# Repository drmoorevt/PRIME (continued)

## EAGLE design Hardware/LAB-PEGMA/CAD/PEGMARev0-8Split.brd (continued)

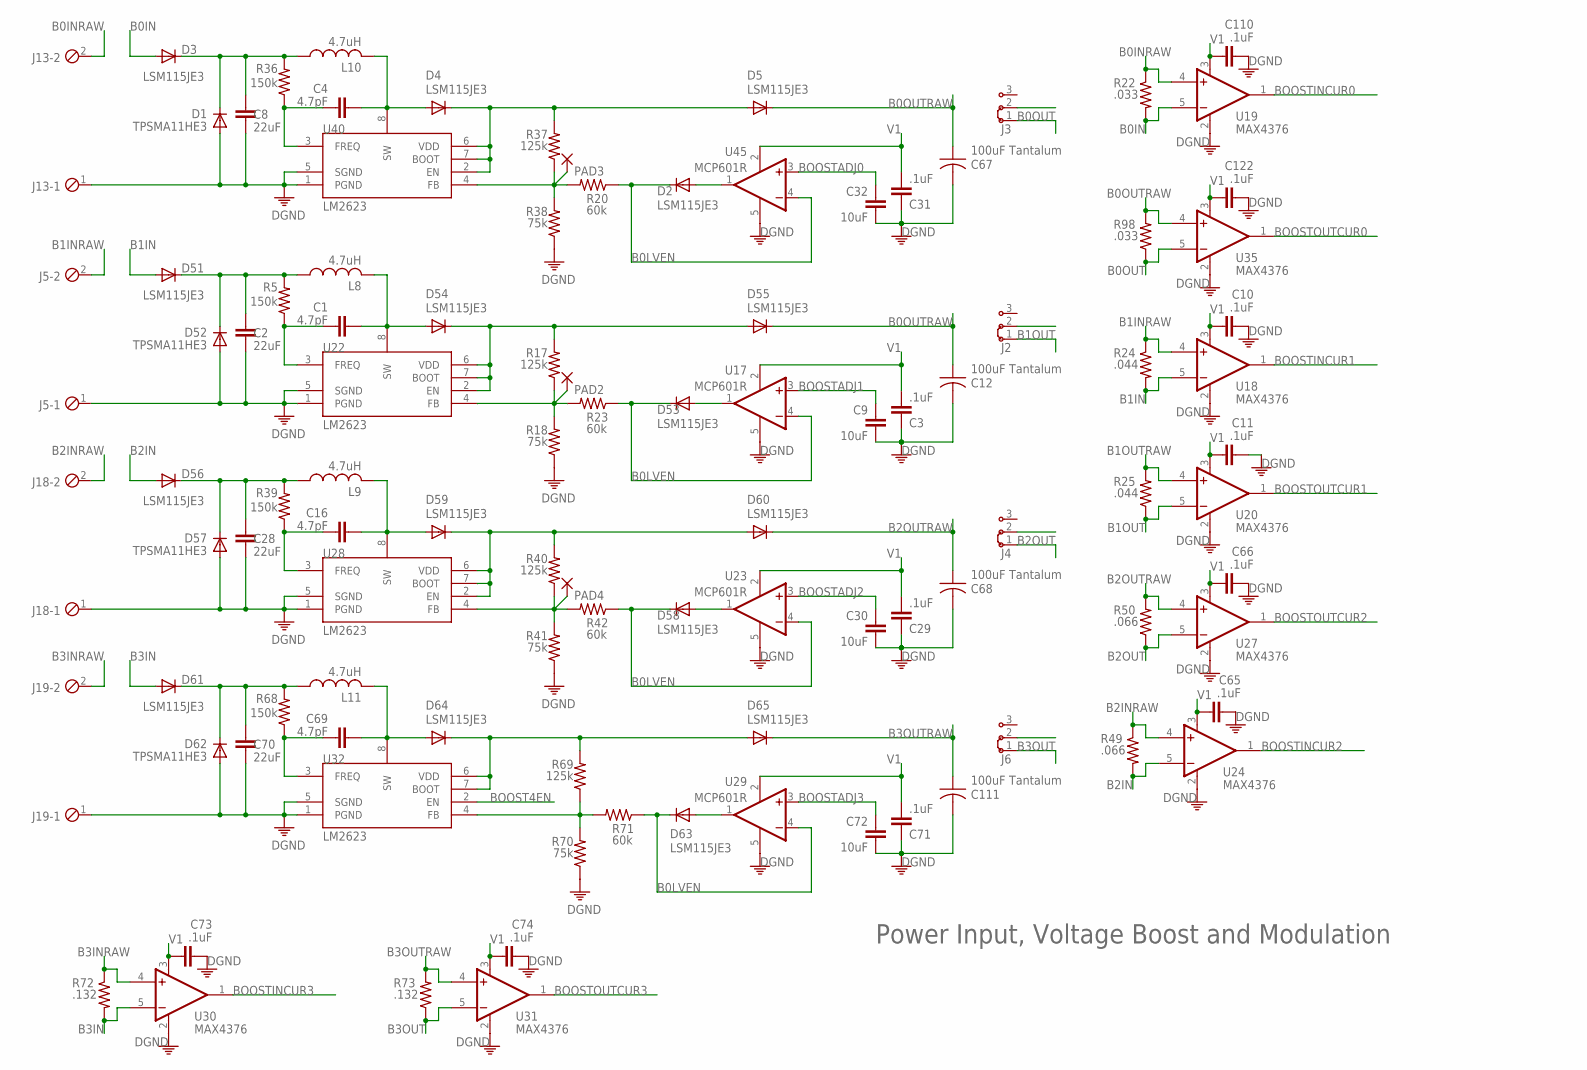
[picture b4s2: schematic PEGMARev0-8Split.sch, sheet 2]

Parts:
C1, C4, C16, C69: 4.7pF; C0603
C2, C8, C28, C70: 22uF; C0603
C3, C10, C11, C29, C31, C65, C66, C71, C73, C74, C110, C122: .1uF; C0603
C9, C30, C32, C72: 10uF; C0603
C12, C67, C68, C111: 100uF Tantalum; C1812
D1, D52, D57, D62: TPSMA11HE3; DO214AC
D2, D3, D4, D5, D51, D53, D54, D55, D56, D58, D59, D60, D61, D63, D64, D65: LSM115JE3; DO214BA
J2, J3, J4, J6: J2X2MM; 04C
J5, J13, J18, J19: MPT2; 2POL254
L8, L9, L10, L11: 4.7uH; L1008/2520METRIC
PAD2, PAD3, PAD4: 2,54/1,0
R5, R36, R39, R68: 150k; R0603
R17, R37, R40, R69: 125k; R0603
R18, R38, R41, R70: 75k; R0603
R20, R23, R42, R71: 60k; R0603
R22, R98: .033; R0603
R24, R25: .044; R0603
R49, R50: .066; R0603
R72, R73: .132; R0603
U17, U23, U29, U45: MCP601R; SOT23-5
U18, U19, U20, U24, U27, U30, U31, U35: MAX4376; SOT23-5
U22, U28, U32, U40: LM2623; MSOP8

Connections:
B0IN: D3.A, R22.2, U19.5 (-IN)
B0INRAW: J13.2, R22.1, U19.4 (+IN); also elsewhere on the board
B0LVEN: D2.C, D53.C, D58.C, D63.C, R20.1, R23.1, R42.1, R71.1, U17.4 (-IN), U23.4 (-IN), U29.4 (-IN), U45.4 (-IN); also elsewhere on the board
B0OUT: J3.1, R98.1, U35.5 (-IN)
B0OUTRAW: C12.1, C67.1, D5.C, D55.C, R98.2, U35.4 (+IN)
B1IN: D51.A, R24.2, U18.5 (-IN)
B1INRAW: J5.2, R24.1, U18.4 (+IN); also elsewhere on the board
B1OUT: J2.1, R25.1, U20.5 (-IN)
B1OUTRAW: R25.2, U20.4 (+IN)
B2IN: D56.A, R49.2, U24.5 (-IN)
B2INRAW: J18.2, R49.1, U24.4 (+IN); also elsewhere on the board
B2OUT: J4.1, R50.1, U27.5 (-IN)
B2OUTRAW: C68.1, D60.C, R50.2, U27.4 (+IN)
B3IN: D61.A, R72.2, U30.5 (-IN)
B3INRAW: J19.2, R72.1, U30.4 (+IN); also elsewhere on the board
B3OUT: J6.1, R73.1, U31.5 (-IN)
B3OUTRAW: C111.1, D65.C, R73.2, U31.4 (+IN)
BOOST4EN: U32.2 (EN); also elsewhere on the board
BOOSTADJ0: C32.1, U45.3 (+IN); also elsewhere on the board
BOOSTADJ1: C9.1, U17.3 (+IN); also elsewhere on the board
BOOSTADJ2: C30.1, U23.3 (+IN); also elsewhere on the board
BOOSTADJ3: C72.1, U29.3 (+IN); also elsewhere on the board
BOOSTINCUR0: U19.1 (OUT); also elsewhere on the board
BOOSTINCUR1: U18.1 (OUT); also elsewhere on the board
BOOSTINCUR2: U24.1 (OUT); also elsewhere on the board
BOOSTINCUR3: U30.1 (OUT); also elsewhere on the board
BOOSTOUTCUR0: U35.1 (OUT); also elsewhere on the board
BOOSTOUTCUR1: U20.1 (OUT); also elsewhere on the board
BOOSTOUTCUR2: U27.1 (OUT); also elsewhere on the board
BOOSTOUTCUR3: U31.1 (OUT); also elsewhere on the board
BUSVOUT: J2.2, J4.2, J6.2; also elsewhere on the board
unnamed: C8.2, D1.C, D3.C, L10.1, R36.2
unnamed: PAD3.1, R20.2, R37.1, R38.2, U40.4 (FB)
unnamed: C4.1, R36.1, U40.3 (FREQ)
unnamed: C2.2, D51.C, D52.C, L8.1, R5.2
unnamed: C4.2, D4.A, L10.2, U40.8 (SW)
unnamed: PAD2.1, R17.1, R18.2, R23.2, U22.4 (FB)
unnamed: C1.1, R5.1, U22.3 (FREQ)
unnamed: C1.2, D54.A, L8.2, U22.8 (SW)
unnamed: D4.C, D5.A, R37.2, U40.2 (EN), U40.6 (VDD), U40.7 (BOOT)
unnamed: D54.C, D55.A, R17.2, U22.2 (EN), U22.6 (VDD), U22.7 (BOOT)
unnamed: D53.A, U17.1 (OUT)
unnamed: D2.A, U45.1 (OUT)
unnamed: C28.2, D56.C, D57.C, L9.1, R39.2
unnamed: PAD4.1, R40.1, R41.2, R42.2, U28.4 (FB)
unnamed: C16.1, R39.1, U28.3 (FREQ)
unnamed: C16.2, D59.A, L9.2, U28.8 (SW)
unnamed: D59.C, D60.A, R40.2, U28.2 (EN), U28.6 (VDD), U28.7 (BOOT)
unnamed: D58.A, U23.1 (OUT)
unnamed: C70.2, D61.C, D62.C, L11.1, R68.2
unnamed: R69.1, R70.2, R71.2, U32.4 (FB)
unnamed: C69.1, R68.1, U32.3 (FREQ)
unnamed: C69.2, D64.A, L11.2, U32.8 (SW)
unnamed: D64.C, D65.A, R69.2, U32.6 (VDD), U32.7 (BOOT)
unnamed: D63.A, U29.1 (OUT)
PE: C2.1, C3.1, C8.1, C9.2, C10.1, C11.1, C12.2, C28.1, C29.1, C30.2, C31.1, C32.2, C65.1, C66.1, C67.2, C68.2, C70.1, C71.1, C72.2, C73.1, C74.1, C110.1, C111.2, C122.1, D1.A, D52.A, D57.A, D62.A, J5.1, J13.1, J18.1, J19.1, R18.1, R38.1, R41.1, R70.1, U17.5 (V-), U18.2 (V-), U19.2 (V-), U20.2 (V-), U22.1 (PGND), U22.5 (SGND), U23.5 (V-), U24.2 (V-), U27.2 (V-), U28.1 (PGND), U28.5 (SGND), U29.5 (V-), U30.2 (V-), U31.2 (V-), U32.1 (PGND), U32.5 (SGND), U35.2 (V-), U40.1 (PGND), U40.5 (SGND), U45.5 (V-); also elsewhere on the board
V1: C3.2, C10.2, C11.2, C29.2, C31.2, C65.2, C66.2, C71.2, C73.2, C74.2, C110.2, C122.2, U17.2 (V+), U18.3 (V+), U19.3 (V+), U20.3 (V+), U23.2 (V+), U24.3 (V+), U27.3 (V+), U29.2 (V+), U30.3 (V+), U31.3 (V+), U35.3 (V+), U45.2 (V+); also elsewhere on the board

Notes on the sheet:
Power Input, Voltage Boost and Modulation

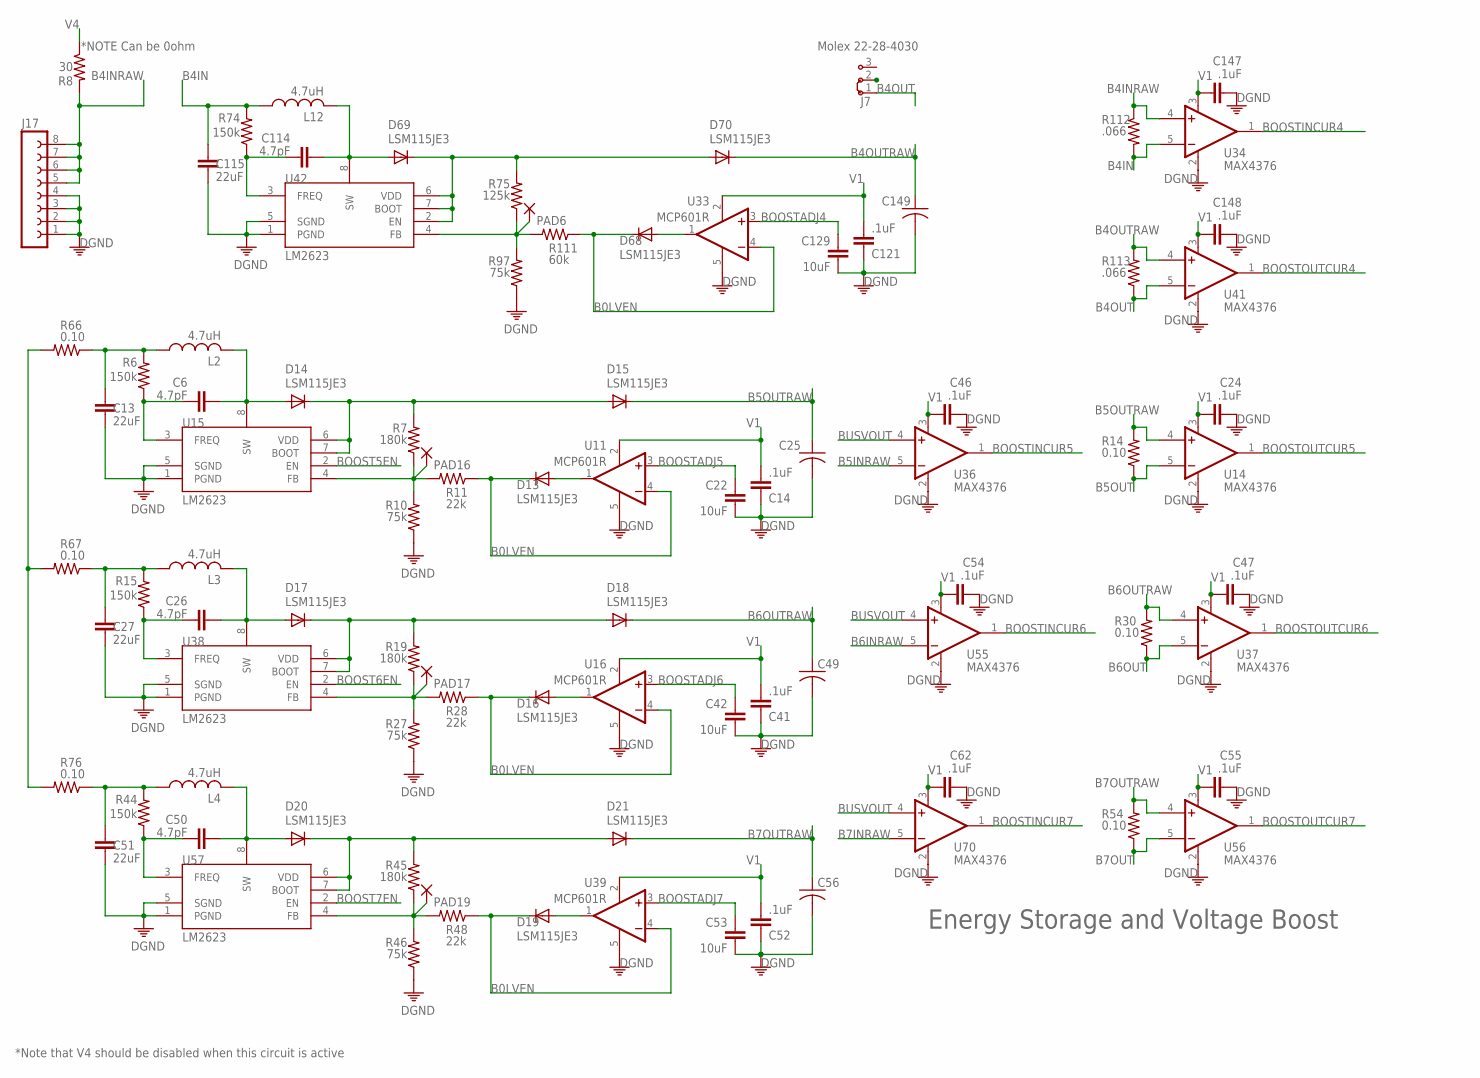
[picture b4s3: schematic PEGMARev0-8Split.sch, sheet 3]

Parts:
C6, C26, C50, C114: 4.7pF; C0603
C13, C27, C51, C115: 22uF; C0603
C14, C24, C41, C46, C47, C52, C54, C55, C62, C121, C147, C148: .1uF; C0603
C22, C42, C53, C129: 10uF; C0603
C25, C49, C56, C149: 100uF Tantalum; C1812
D13, D14, D15, D16, D17, D18, D19, D20, D21, D68, D69, D70: LSM115JE3; DO214BA
J7: Molex 22-28-4030; 04C
J17: FE08-1; FE08
L2, L3, L4, L12: 4.7uH; L1008/2520METRIC
PAD6, PAD16, PAD17, PAD19: 2,54/1,0
R6, R15, R44, R74: 150k; R0603
R7, R19, R45: 180k; R0603
R8: 30; R0603
R10, R27, R46, R97: 75k; R0603
R11, R28, R48: 22k; R0603
R14, R30, R54, R66, R67, R76: 0.10; R0603
R75: 125k; R0603
R111: 60k; R0603
R112, R113: .066; R0603
U11, U16, U33, U39: MCP601R; SOT23-5
U14, U34, U36, U37, U41, U55, U56, U70: MAX4376; SOT23-5
U15, U38, U42, U57: LM2623; MSOP8

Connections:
B0LVEN: D13.C, D16.C, D19.C, D68.C, R11.1, R28.1, R48.1, R111.1, U11.4 (-IN), U16.4 (-IN), U33.4 (-IN), U39.4 (-IN); also elsewhere on the board
B4IN: C115.2, L12.1, R74.2, R112.2, U34.5 (-IN)
B4INRAW: J17.5, J17.6, J17.7, J17.8, R8.2, R112.1, U34.4 (+IN); also elsewhere on the board
B4OUT: J7.1, R113.1, U41.5 (-IN)
B4OUTRAW: C149.1, D70.C, R113.2, U41.4 (+IN)
B5INRAW: C13.2, L2.1, R6.2, R66.1, U36.5 (-IN)
B5OUT: R14.1, U14.5 (-IN); also elsewhere on the board
B5OUTRAW: C25.1, D15.C, R14.2, U14.4 (+IN)
B6INRAW: C27.2, L3.1, R15.2, R67.1, U55.5 (-IN)
B6OUT: R30.1, U37.5 (-IN); also elsewhere on the board
B6OUTRAW: C49.1, D18.C, R30.2, U37.4 (+IN)
B7INRAW: C51.2, L4.1, R44.2, R76.1, U70.5 (-IN)
B7OUT: R54.1, U56.5 (-IN); also elsewhere on the board
B7OUTRAW: C56.1, D21.C, R54.2, U56.4 (+IN)
BOOST5EN: U15.2 (EN); also elsewhere on the board
BOOST6EN: U38.2 (EN); also elsewhere on the board
BOOST7EN: U57.2 (EN); also elsewhere on the board
BOOSTADJ4: C129.1, U33.3 (+IN); also elsewhere on the board
BOOSTADJ5: C22.1, U11.3 (+IN); also elsewhere on the board
BOOSTADJ6: C42.1, U16.3 (+IN); also elsewhere on the board
BOOSTADJ7: C53.1, U39.3 (+IN); also elsewhere on the board
BOOSTINCUR4: U34.1 (OUT); also elsewhere on the board
BOOSTINCUR5: U36.1 (OUT); also elsewhere on the board
BOOSTINCUR6: U55.1 (OUT); also elsewhere on the board
BOOSTINCUR7: U70.1 (OUT); also elsewhere on the board
BOOSTOUTCUR4: U41.1 (OUT); also elsewhere on the board
BOOSTOUTCUR5: U14.1 (OUT); also elsewhere on the board
BOOSTOUTCUR6: U37.1 (OUT); also elsewhere on the board
BOOSTOUTCUR7: U56.1 (OUT); also elsewhere on the board
BUSVOUT: J7.2, R66.2, R67.2, R76.2, U36.4 (+IN), U55.4 (+IN), U70.4 (+IN); also elsewhere on the board
unnamed: PAD16.1, R7.1, R10.2, R11.2, U15.4 (FB)
unnamed: C6.1, R6.1, U15.3 (FREQ)
unnamed: C6.2, D14.A, L2.2, U15.8 (SW)
unnamed: D14.C, D15.A, R7.2, U15.6 (VDD), U15.7 (BOOT)
unnamed: D13.A, U11.1 (OUT)
unnamed: PAD17.1, R19.1, R27.2, R28.2, U38.4 (FB)
unnamed: C26.1, R15.1, U38.3 (FREQ)
unnamed: C26.2, D17.A, L3.2, U38.8 (SW)
unnamed: D17.C, D18.A, R19.2, U38.6 (VDD), U38.7 (BOOT)
unnamed: D16.A, U16.1 (OUT)
unnamed: PAD19.1, R45.1, R46.2, R48.2, U57.4 (FB)
unnamed: C50.1, R44.1, U57.3 (FREQ)
unnamed: C50.2, D20.A, L4.2, U57.8 (SW)
unnamed: D20.C, D21.A, R45.2, U57.6 (VDD), U57.7 (BOOT)
unnamed: D19.A, U39.1 (OUT)
unnamed: PAD6.1, R75.1, R97.2, R111.2, U42.4 (FB)
unnamed: C114.1, R74.1, U42.3 (FREQ)
unnamed: C114.2, D69.A, L12.2, U42.8 (SW)
unnamed: D69.C, D70.A, R75.2, U42.2 (EN), U42.6 (VDD), U42.7 (BOOT)
unnamed: D68.A, U33.1 (OUT)
PE: C13.1, C14.1, C22.2, C24.1, C25.2, C27.1, C41.1, C42.2, C46.1, C47.1, C49.2, C51.1, C52.1, C53.2, C54.1, C55.1, C56.2, C62.1, C115.1, C121.1, C129.2, C147.1, C148.1, C149.2, J17.1, J17.2, J17.3, J17.4, R10.1, R27.1, R46.1, R97.1, U11.5 (V-), U14.2 (V-), U15.1 (PGND), U15.5 (SGND), U16.5 (V-), U33.5 (V-), U34.2 (V-), U36.2 (V-), U37.2 (V-), U38.1 (PGND), U38.5 (SGND), U39.5 (V-), U41.2 (V-), U42.1 (PGND), U42.5 (SGND), U55.2 (V-), U56.2 (V-), U57.1 (PGND), U57.5 (SGND), U70.2 (V-); also elsewhere on the board
V1: C14.2, C24.2, C41.2, C46.2, C47.2, C52.2, C54.2, C55.2, C62.2, C121.2, C147.2, C148.2, U11.2 (V+), U14.3 (V+), U16.2 (V+), U33.2 (V+), U34.3 (V+), U36.3 (V+), U37.3 (V+), U39.2 (V+), U41.3 (V+), U55.3 (V+), U56.3 (V+), U70.3 (V+); also elsewhere on the board
V4: R8.1; also elsewhere on the board

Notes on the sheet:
Energy Storage and Voltage Boost
*Note that V4 should be disabled when this circuit is active
*NOTE Can be 0ohm

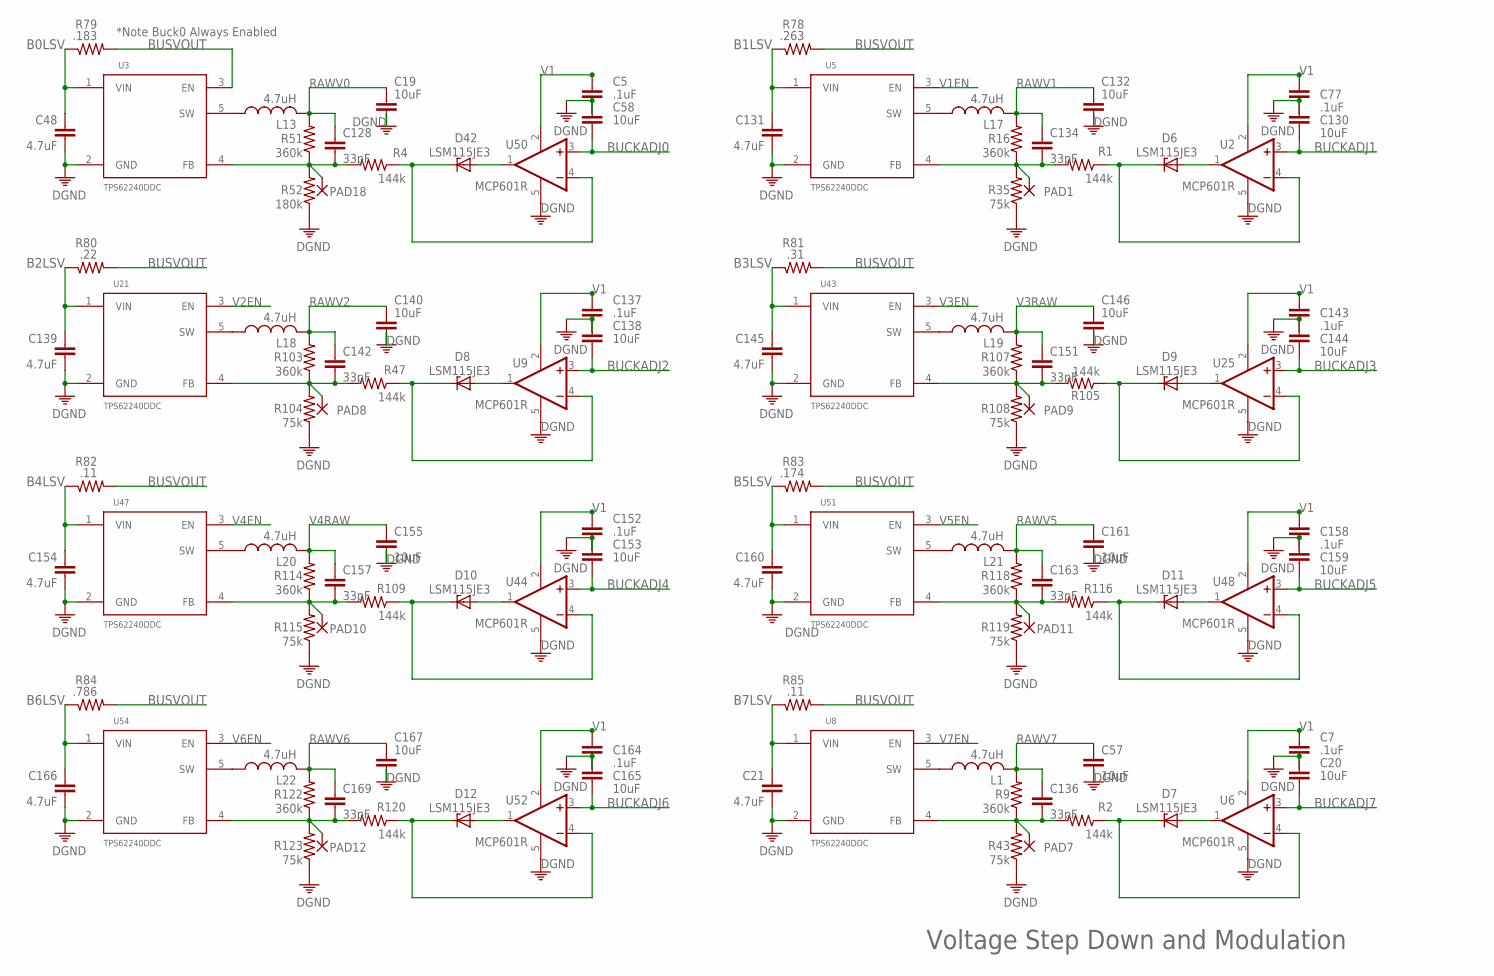
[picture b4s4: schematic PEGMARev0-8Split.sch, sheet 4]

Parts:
C5, C7, C77, C137, C143, C152, C158, C164: .1uF; C0603
C19, C20, C57, C58, C130, C132, C138, C140, C144, C146, C153, C155, C159, C161, C165, C167: 10uF; C0603
C21, C48, C131, C139, C145, C154, C160, C166: 4.7uF; C0603
C128, C134, C136, C142, C151, C157, C163, C169: 33pF; C0603
D6, D7, D8, D9, D10, D11, D12, D42: LSM115JE3; DO214BA
L1, L13, L17, L18, L19, L20, L21, L22: 4.7uH; L1008/2520METRIC
PAD1, PAD7, PAD8, PAD9, PAD10, PAD11, PAD12, PAD18: 2,54/1,0
R1, R2, R4, R47, R105, R109, R116, R120: 144k; R0603
R9, R16, R51, R103, R107, R114, R118, R122: 360k; R0603
R35, R43, R104, R108, R115, R119, R123: 75k; R0603
R52: 180k; R0603
R78: .263; R0603
R79: .183; R0603
R80: .22; R0603
R81: .31; R0603
R82, R85: .11; R0603
R83: .174; R0603
R84: .786; R0603
U2, U6, U9, U25, U44, U48, U50, U52: MCP601R; SOT23-5
U3, U5, U8, U21, U43, U47, U51, U54: TPS62240DDC; SOT23-5

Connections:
B0LSV: C48.1, R79.1, U3.1 (VIN)
B1LSV: C131.1, R78.1, U5.1 (VIN); also elsewhere on the board
B2LSV: C139.1, R80.1, U21.1 (VIN); also elsewhere on the board
B3LSV: C145.1, R81.1, U43.1 (VIN); also elsewhere on the board
B4LSV: C154.1, R82.1, U47.1 (VIN); also elsewhere on the board
B5LSV: C160.1, R83.1, U51.1 (VIN); also elsewhere on the board
B6LSV: C166.1, R84.1, U54.1 (VIN); also elsewhere on the board
B7LSV: C21.1, R85.1, U8.1 (VIN); also elsewhere on the board
BUCKADJ0: C58.1, U50.3 (+IN); also elsewhere on the board
BUCKADJ1: C130.1, U2.3 (+IN); also elsewhere on the board
BUCKADJ2: C138.1, U9.3 (+IN); also elsewhere on the board
BUCKADJ3: C144.1, U25.3 (+IN); also elsewhere on the board
BUCKADJ4: C153.1, U44.3 (+IN); also elsewhere on the board
BUCKADJ5: C159.1, U48.3 (+IN); also elsewhere on the board
BUCKADJ6: C165.1, U52.3 (+IN); also elsewhere on the board
BUCKADJ7: C20.1, U6.3 (+IN); also elsewhere on the board
BUSVOUT: R78.2, R79.2, R80.2, R81.2, R82.2, R83.2, R84.2, R85.2, U3.3 (EN); also elsewhere on the board
unnamed: D42.C, R4.1, U50.4 (-IN)
unnamed: L13.1, U3.5 (SW)
unnamed: D7.C, R2.1, U6.4 (-IN)
unnamed: C136.2, PAD7.1, R2.2, R9.1, R43.2, U8.4 (FB)
unnamed: L1.1, U8.5 (SW)
unnamed: D6.C, R1.1, U2.4 (-IN)
unnamed: D7.A, U6.1 (OUT)
unnamed: C134.2, PAD1.1, R1.2, R16.1, R35.2, U5.4 (FB)
unnamed: C128.2, PAD18.1, R4.2, R51.1, R52.2, U3.4 (FB)
unnamed: L17.1, U5.5 (SW)
unnamed: D6.A, U2.1 (OUT)
unnamed: D8.C, R47.1, U9.4 (-IN)
unnamed: C142.2, PAD8.1, R47.2, R103.1, R104.2, U21.4 (FB)
unnamed: L18.1, U21.5 (SW)
unnamed: D8.A, U9.1 (OUT)
unnamed: D42.A, U50.1 (OUT)
unnamed: D9.C, R105.1, U25.4 (-IN)
unnamed: C151.2, PAD9.1, R105.2, R107.1, R108.2, U43.4 (FB)
unnamed: L19.1, U43.5 (SW)
unnamed: D9.A, U25.1 (OUT)
unnamed: D10.C, R109.1, U44.4 (-IN)
unnamed: C157.2, PAD10.1, R109.2, R114.1, R115.2, U47.4 (FB)
unnamed: L20.1, U47.5 (SW)
unnamed: D10.A, U44.1 (OUT)
unnamed: D11.C, R116.1, U48.4 (-IN)
unnamed: C163.2, PAD11.1, R116.2, R118.1, R119.2, U51.4 (FB)
unnamed: L21.1, U51.5 (SW)
unnamed: D11.A, U48.1 (OUT)
unnamed: D12.C, R120.1, U52.4 (-IN)
unnamed: C169.2, PAD12.1, R120.2, R122.1, R123.2, U54.4 (FB)
unnamed: L22.1, U54.5 (SW)
unnamed: D12.A, U52.1 (OUT)
PE: C5.1, C7.1, C19.2, C20.2, C21.2, C48.2, C57.2, C58.2, C77.1, C130.2, C131.2, C132.2, C137.1, C138.2, C139.2, C140.2, C143.1, C144.2, C145.2, C146.2, C152.1, C153.2, C154.2, C155.2, C158.1, C159.2, C160.2, C161.2, C164.1, C165.2, C166.2, C167.2, R35.1, R43.1, R52.1, R104.1, R108.1, R115.1, R119.1, R123.1, U2.5 (V-), U3.2 (GND), U5.2 (GND), U6.5 (V-), U8.2 (GND), U9.5 (V-), U21.2 (GND), U25.5 (V-), U43.2 (GND), U44.5 (V-), U47.2 (GND), U48.5 (V-), U50.5 (V-), U51.2 (GND), U52.5 (V-), U54.2 (GND); also elsewhere on the board
RAWV0: C19.1, C128.1, L13.2, R51.2; also elsewhere on the board
RAWV1: C132.1, C134.1, L17.2, R16.2; also elsewhere on the board
RAWV2: C140.1, C142.1, L18.2, R103.2; also elsewhere on the board
RAWV5: C161.1, C163.1, L21.2, R118.2; also elsewhere on the board
RAWV6: C167.1, C169.1, L22.2, R122.2; also elsewhere on the board
RAWV7: C57.1, C136.1, L1.2, R9.2; also elsewhere on the board
V1: C5.2, C7.2, C77.2, C137.2, C143.2, C152.2, C158.2, C164.2, U2.2 (V+), U6.2 (V+), U9.2 (V+), U25.2 (V+), U44.2 (V+), U48.2 (V+), U50.2 (V+), U52.2 (V+); also elsewhere on the board
V1EN: U5.3 (EN); also elsewhere on the board
V2EN: U21.3 (EN); also elsewhere on the board
V3EN: U43.3 (EN); also elsewhere on the board
V3RAW: C146.1, C151.1, L19.2, R107.2
V4EN: U47.3 (EN); also elsewhere on the board
V4RAW: C155.1, C157.1, L20.2, R114.2
V5EN: U51.3 (EN); also elsewhere on the board
V6EN: U54.3 (EN); also elsewhere on the board
V7EN: U8.3 (EN); also elsewhere on the board

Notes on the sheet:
*Note Buck0 Always Enabled
Voltage Step Down and Modulation

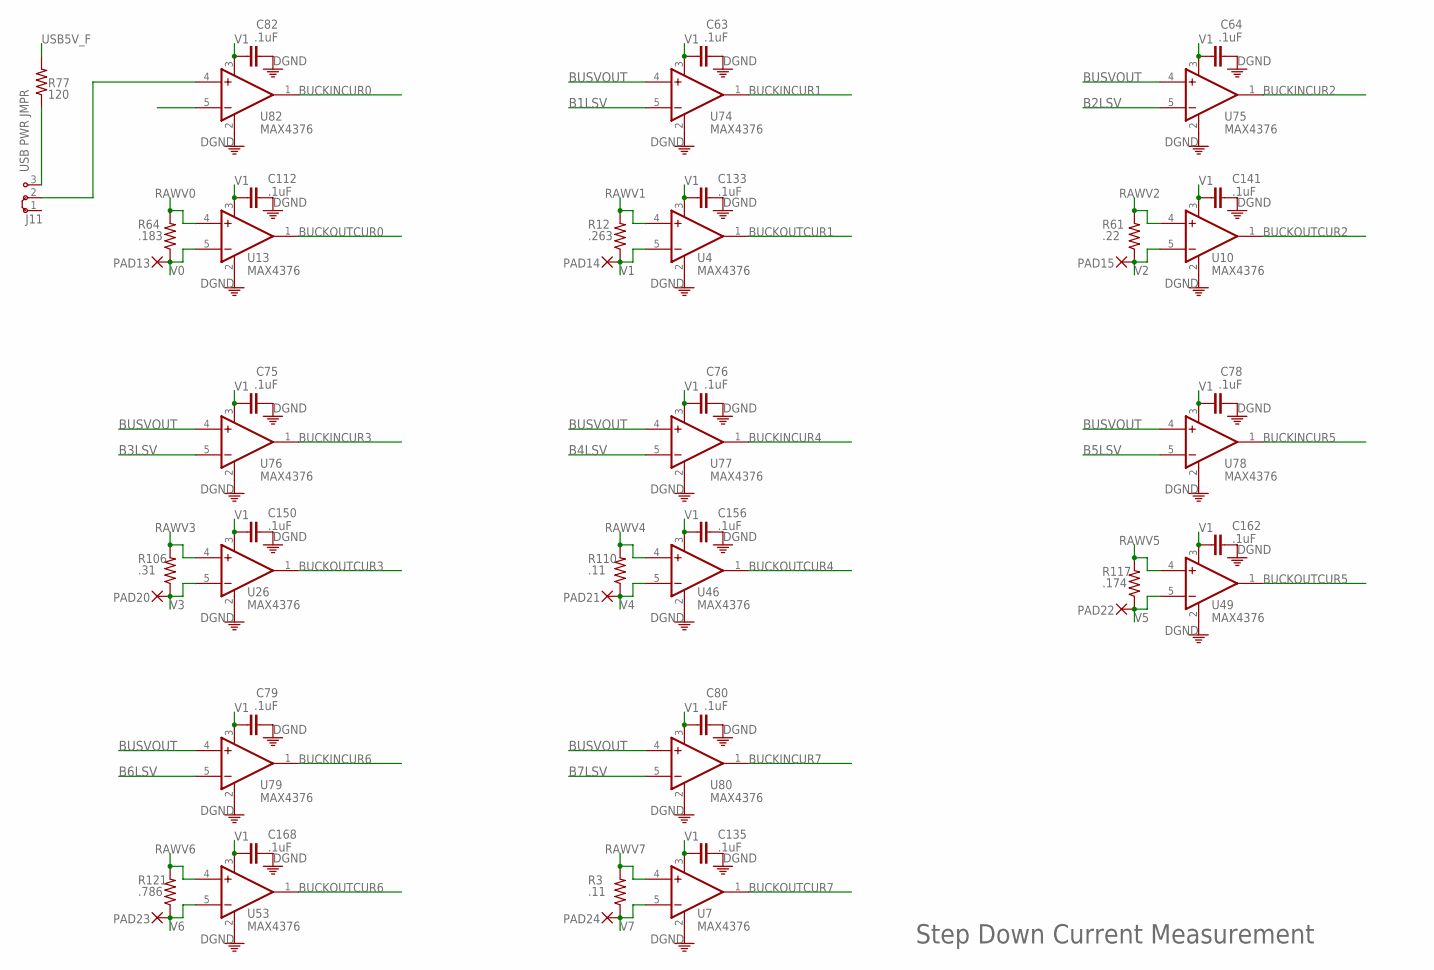
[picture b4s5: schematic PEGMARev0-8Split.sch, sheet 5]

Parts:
C63, C64, C75, C76, C78, C79, C80, C82, C112, C133, C135, C141, C150, C156, C162, C168: .1uF; C0603
J11: J2X2MM; 04C
PAD13, PAD14, PAD15, PAD20, PAD21, PAD22, PAD23, PAD24: 2,54/1,0
R3, R110: .11; R0603
R12: .263; R0603
R61: .22; R0603
R64: .183; R0603
R77: 120; M1206
R106: .31; R0603
R117: .174; R0603
R121: .786; R0603
U4, U7, U10, U13, U26, U46, U49, U53, U74, U75, U76, U77, U78, U79, U80, U82: MAX4376; SOT23-5

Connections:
B1LSV: U74.5 (-IN); also elsewhere on the board
B2LSV: U75.5 (-IN); also elsewhere on the board
B3LSV: U76.5 (-IN); also elsewhere on the board
B4LSV: U77.5 (-IN); also elsewhere on the board
B5LSV: U78.5 (-IN); also elsewhere on the board
B6LSV: U79.5 (-IN); also elsewhere on the board
B7LSV: U80.5 (-IN); also elsewhere on the board
BUCKINCUR0: U82.1 (OUT); also elsewhere on the board
BUCKINCUR1: U74.1 (OUT); also elsewhere on the board
BUCKINCUR2: U75.1 (OUT); also elsewhere on the board
BUCKINCUR3: U76.1 (OUT); also elsewhere on the board
BUCKINCUR4: U77.1 (OUT); also elsewhere on the board
BUCKINCUR5: U78.1 (OUT); also elsewhere on the board
BUCKINCUR6: U79.1 (OUT); also elsewhere on the board
BUCKINCUR7: U80.1 (OUT); also elsewhere on the board
BUCKOUTCUR0: U13.1 (OUT); also elsewhere on the board
BUCKOUTCUR1: U4.1 (OUT); also elsewhere on the board
BUCKOUTCUR2: U10.1 (OUT); also elsewhere on the board
BUCKOUTCUR3: U26.1 (OUT); also elsewhere on the board
BUCKOUTCUR4: U46.1 (OUT); also elsewhere on the board
BUCKOUTCUR5: U49.1 (OUT); also elsewhere on the board
BUCKOUTCUR6: U53.1 (OUT); also elsewhere on the board
BUCKOUTCUR7: U7.1 (OUT); also elsewhere on the board
BUSVOUT: J11.2, U74.4 (+IN), U76.4 (+IN), U77.4 (+IN), U78.4 (+IN), U80.4 (+IN), U82.4 (+IN); also elsewhere on the board
PE: C63.1, C64.1, C75.1, C76.1, C78.1, C79.1, C80.1, C82.1, C112.1, C133.1, C135.1, C141.1, C150.1, C156.1, C162.1, C168.1, U4.2 (V-), U7.2 (V-), U10.2 (V-), U13.2 (V-), U26.2 (V-), U46.2 (V-), U49.2 (V-), U53.2 (V-), U74.2 (V-), U75.2 (V-), U76.2 (V-), U77.2 (V-), U78.2 (V-), U79.2 (V-), U80.2 (V-), U82.2 (V-); also elsewhere on the board
RAWV0: R64.2, U13.4 (+IN); also elsewhere on the board
RAWV1: R12.2, U4.4 (+IN); also elsewhere on the board
RAWV2: R61.2, U10.4 (+IN); also elsewhere on the board
RAWV3: R106.2, U26.4 (+IN)
RAWV4: R110.2, U46.4 (+IN)
RAWV5: R117.2, U49.4 (+IN); also elsewhere on the board
RAWV6: R121.2, U53.4 (+IN); also elsewhere on the board
RAWV7: R3.2, U7.4 (+IN); also elsewhere on the board
USB5V_F: J11.3, R77.1, R77.2; also elsewhere on the board
V0: PAD13.1, R64.1, U13.5 (-IN); also elsewhere on the board
V1: C63.2, C64.2, C75.2, C76.2, C78.2, C79.2, C80.2, C82.2, C112.2, C133.2, C135.2, C141.2, C150.2, C156.2, C162.2, C168.2, PAD14.1, R12.1, U4.3 (V+), U4.5 (-IN), U7.3 (V+), U10.3 (V+), U13.3 (V+), U26.3 (V+), U46.3 (V+), U49.3 (V+), U53.3 (V+), U74.3 (V+), U75.3 (V+), U76.3 (V+), U77.3 (V+), U78.3 (V+), U79.3 (V+), U80.3 (V+), U82.3 (V+); also elsewhere on the board
V2: PAD15.1, R61.1, U10.5 (-IN); also elsewhere on the board
V3: PAD20.1, R106.1, U26.5 (-IN); also elsewhere on the board
V4: PAD21.1, R110.1, U46.5 (-IN); also elsewhere on the board
V5: PAD22.1, R117.1, U49.5 (-IN); also elsewhere on the board
V6: PAD23.1, R121.1, U53.5 (-IN); also elsewhere on the board
V7: PAD24.1, R3.1, U7.5 (-IN); also elsewhere on the board

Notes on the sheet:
USB PWR JMPR
Step Down Current Measurement

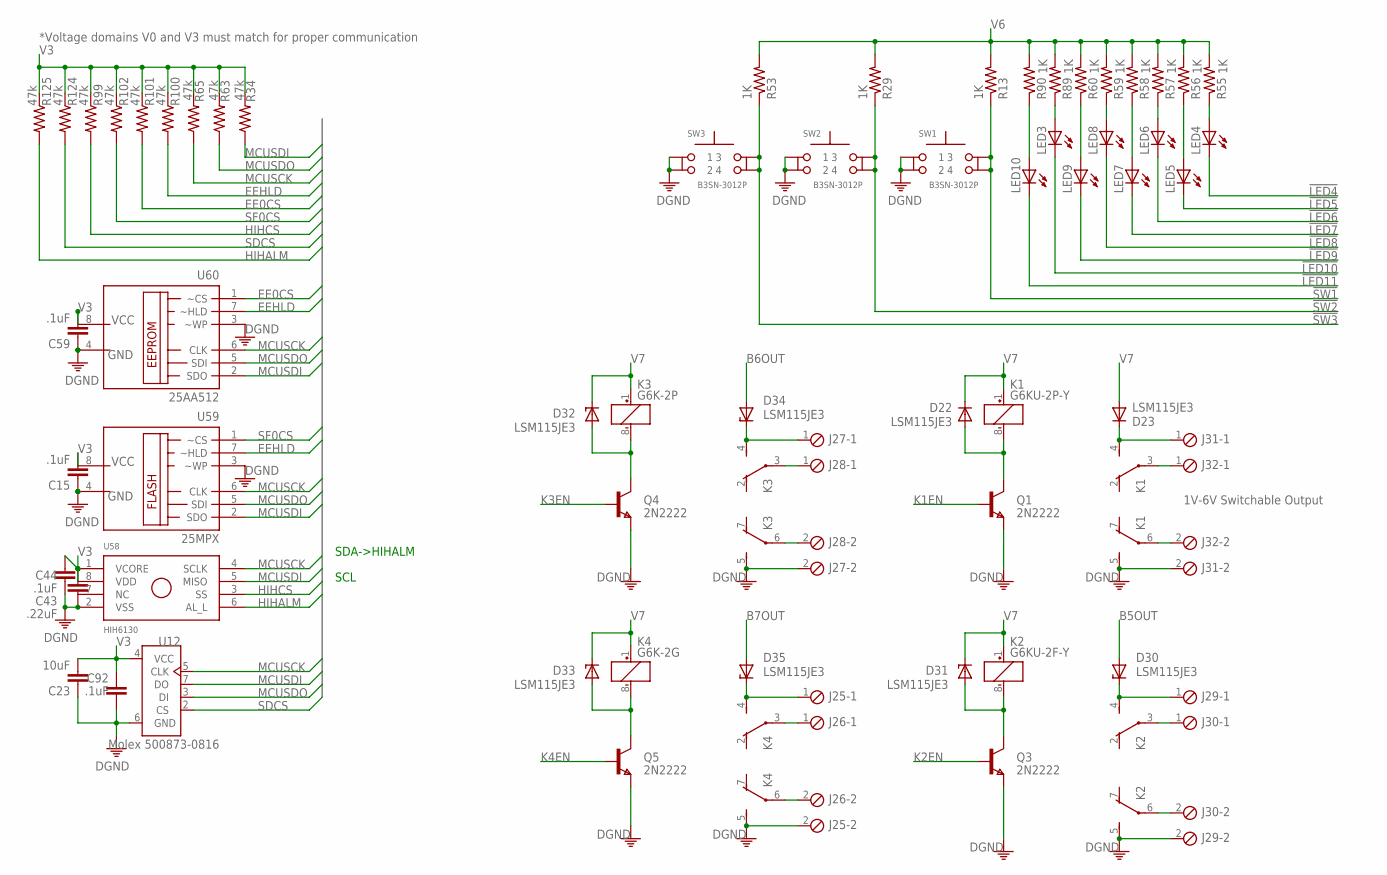
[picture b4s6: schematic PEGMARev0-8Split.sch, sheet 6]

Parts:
C15, C44, C59, C92: .1uF; C0603
C23: 10uF; C0603
C43: .22uF; C0603
D22, D23, D30, D31, D32, D33, D34, D35: LSM115JE3; DO214BA
J25, J26, J27, J28, J29, J30, J31, J32: MPT2; 2POL254
K1: G6KU-2P-Y
K2: G6KU-2F-Y
K3: G6K-2P
K4: G6K-2G
LED3, LED4, LED5, LED6, LED7, LED8, LED9, LED10: LEDCHIPLED_1206; CHIPLED_1206
Q1, Q3, Q4, Q5: 2N2222; SOT323
R13, R29, R53, R55, R56, R57, R58, R59, R60, R89, R90: 1K; R0603
R34, R63, R65, R99, R100, R101, R102, R124, R125: 47k; R0603
SW1, SW2, SW3: B3SN-3012P; SWITCH(B3SN)
U12: Molex 500873-0816; MICROSD
U58: HIH6130; SO-08M
U59: 25MPX; SO-08M
U60: 25AA512; SO-08M

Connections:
!LED4: LED4.C; also elsewhere on the board
!LED5: LED5.C; also elsewhere on the board
!LED6: LED6.C; also elsewhere on the board
!LED7: LED7.C; also elsewhere on the board
!LED8: LED8.C; also elsewhere on the board
!LED9: LED9.C; also elsewhere on the board
!LED10: LED3.C; also elsewhere on the board
!LED11: LED10.C; also elsewhere on the board
!SW1: R13.1, SW1.3, SW1.4; also elsewhere on the board
!SW2: R29.1, SW2.3, SW2.4; also elsewhere on the board
!SW3: R53.1, SW3.3, SW3.4; also elsewhere on the board
B5OUT: D30.A; also elsewhere on the board
B6OUT: D34.A; also elsewhere on the board
B7OUT: D35.A; also elsewhere on the board
EE0CS: R101.2, U60.1 (~CS); also elsewhere on the board
EEHLD: R100.2, U59.7 (~HLD), U60.7 (~HLD); also elsewhere on the board
HIHALM: R125.2, U58.6 (AL_L); also elsewhere on the board
HIHCS: R99.2, U58.3 (SS); also elsewhere on the board
K1EN: Q1.2 (B); also elsewhere on the board
K2EN: Q3.2 (B); also elsewhere on the board
K3EN: Q4.2 (B); also elsewhere on the board
K4EN: Q5.2 (B); also elsewhere on the board
MCUSCK: R65.1, U12.5 (CLK), U58.4 (SCLK), U59.6 (CLK), U60.6 (CLK); also elsewhere on the board
MCUSDI: R34.1, U12.7 (DO), U58.5 (MISO), U59.2 (SDO), U60.2 (SDO); also elsewhere on the board
MCUSDO: R63.1, U12.3 (DI), U59.5 (SDI), U60.5 (SDI); also elsewhere on the board
unnamed: D31.A, K2.8 (-), Q3.1 (C)
unnamed: D22.A, K1.8 (-), Q1.1 (C)
unnamed: LED3.A, R89.1
unnamed: LED4.A, R55.1
unnamed: LED5.A, R56.1
unnamed: LED6.A, R57.1
unnamed: LED10.A, R90.1
unnamed: LED7.A, R58.1
unnamed: LED8.A, R59.1
unnamed: LED9.A, R60.1
unnamed: J32.1, K1.3
unnamed: J32.2, K1.6
unnamed: D32.A, K3.8 (-), Q4.1 (C)
unnamed: J28.1, K3.3
unnamed: D23.C, J31.1, K1.4 (S)
unnamed: J28.2, K3.6
unnamed: D33.A, K4.8 (-), Q5.1 (C)
unnamed: J30.1, K2.3
unnamed: D30.C, J29.1, K2.4 (S)
unnamed: J30.2, K2.6
unnamed: D34.C, J27.1, K3.4 (S)
unnamed: D35.C, J25.1, K4.4 (S)
unnamed: J26.1, K4.3
unnamed: J26.2, K4.6
PE: C15.1, C23.1, C43.1, C44.1, C59.1, C92.2, J25.2, J27.2, J29.2, J31.2, K1.5 (S), K2.5 (S), K3.5 (S), K4.5 (S), Q1.3 (E), Q3.3 (E), Q4.3 (E), Q5.3 (E), SW1.1, SW1.2, SW2.1, SW2.2, SW3.1, SW3.2, U12.6 (GND), U58.2 (VSS), U59.3 (~WP), U59.4 (GND), U60.3 (~WP), U60.4 (GND); also elsewhere on the board
SDCS: R124.2, U12.2 (CS); also elsewhere on the board
SF0CS: R102.2, U59.1 (~CS); also elsewhere on the board
V3: C15.2, C23.2, C43.2, C44.2, C59.2, C92.1, R34.2, R63.2, R65.2, R99.1, R100.1, R101.1, R102.1, R124.1, R125.1, U12.4 (VCC), U58.1 (VCORE), U58.8 (VDD), U59.8 (VCC), U60.8 (VCC); also elsewhere on the board
V6: R13.2, R29.2, R53.2, R55.2, R56.2, R57.2, R58.2, R59.2, R60.2, R89.2, R90.2; also elsewhere on the board
V7: D22.C, D23.A, D31.C, D32.C, D33.C, K1.1 (+), K2.1 (+), K3.1 (+), K4.1 (+); also elsewhere on the board

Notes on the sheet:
*Voltage domains V0 and V3 must match for proper communication
SDA->HIHALM
SCL
1V-6V Switchable Output

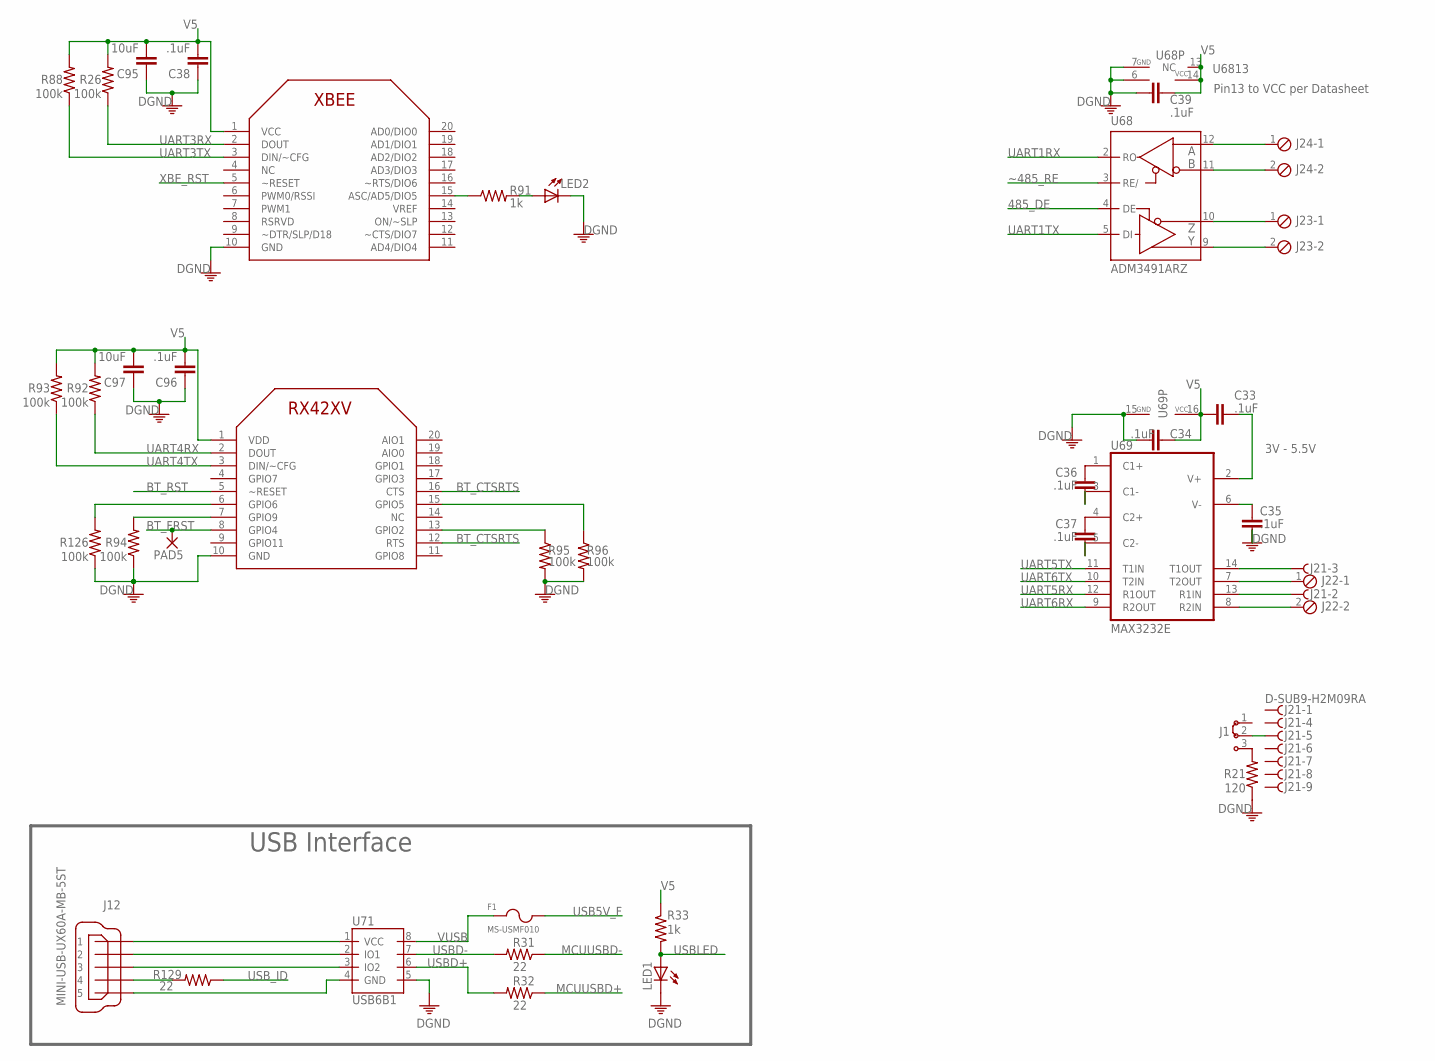
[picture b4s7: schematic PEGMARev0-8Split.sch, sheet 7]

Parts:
C33, C34, C35, C36, C37, C38, C39, C96: .1uF; C0603
C95, C97: 10uF; C0603
F1: MS-USMF010; FUSE(1210)
J1: J2X2MM; 04C
J12: MINI-USB-UX60A-MB-5ST; UX60A-MB-5ST
J21: D-SUB9-H2M09RA; H2M09RA
J22, J23, J24: MPT2; 2POL254
LED1, LED2: LEDCHIPLED_1206; CHIPLED_1206
PAD5: 2,54/1,0
R21: 120; R1206
R26, R88, R92, R93, R94, R95, R96, R126: 100k; R0603
R31, R32, R129: 22; R0603
R33, R91: 1k; R0603
U68: ADM3491ARZ; SO14
U69: MAX3232E; SO16L
U71: USB6B1; SO08
U81: RN42XV
U$25: XBEE802.15.4; XBEE

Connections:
485_DE: U68.4 (DE); also elsewhere on the board
BT_CTSRTS: U81.12 (RTS), U81.16 (CTS)
BT_FRST: PAD5.1, U81.8 (GPIO4)
BT_RST: U81.5 (~RESET); also elsewhere on the board
MCUUSBD+: R32.1; also elsewhere on the board
MCUUSBD-: R31.1; also elsewhere on the board
unnamed: J22.1, U69.7 (T2OUT)
unnamed: J22.2, U69.8 (R2IN)
unnamed: R126.2, U81.6 (GPIO6)
unnamed: R94.2, U81.7 (GPIO9)
unnamed: R95.1, U81.13 (GPIO2)
unnamed: J1.2, J21.5
unnamed: C33.1, U69.2 (V+)
unnamed: C35.1, U69.6 (V-)
unnamed: C36.1, U69.1 (C1+)
unnamed: C36.2, U69.3 (C1-)
unnamed: C37.1, U69.4 (C2+)
unnamed: C37.2, U69.5 (C2-)
unnamed: J21.3, U69.14 (T1OUT)
unnamed: J21.2, U69.13 (R1IN)
unnamed: J1.3, R21.2
unnamed: J12.4, R129.2
unnamed: R91.1, U$25.15 (ASC/AD5/DIO5)
unnamed: LED2.A, R91.2
unnamed: R96.1, U81.15 (GPIO5)
unnamed: J24.1, U68.12 (A)
unnamed: J24.2, U68.11 (B)
unnamed: J23.1, U68.10 (Z)
unnamed: J23.2, U68.9 (Y)
unnamed: J12.1, U71.1 (VCC)
unnamed: J12.2, U71.2 (IO1)
unnamed: J12.3, U71.3 (IO2)
unnamed: J12.5, U71.4 (GND)
PE: C34.2, C35.2, C38.1, C39.2, C95.1, C96.1, C97.1, LED1.C, LED2.C, R21.1, R94.1, R95.2, R96.2, R126.1, U68.6 (GND), U68.7 (GND), U69.15 (GND), U71.5 (GND), U81.10 (GND), U$25.10 (GND); also elsewhere on the board
UART1RX: U68.2 (RO); also elsewhere on the board
UART1TX: U68.5 (DI); also elsewhere on the board
UART3RX: R26.1, U$25.2 (DOUT); also elsewhere on the board
UART3TX: R88.1, U$25.3 (DIN/~CFG); also elsewhere on the board
UART4RX: R92.1, U81.2 (DOUT); also elsewhere on the board
UART4TX: R93.1, U81.3 (DIN/~CFG); also elsewhere on the board
UART5RX: U69.12 (R1OUT); also elsewhere on the board
UART5TX: U69.11 (T1IN); also elsewhere on the board
UART6RX: U69.9 (R2OUT); also elsewhere on the board
UART6TX: U69.10 (T2IN); also elsewhere on the board
USB5V_F: F1.P$1; also elsewhere on the board
USBD+: R32.2, U71.6 (IO2)
USBD-: R31.2, U71.7 (IO1)
USBLED: LED1.A, R33.2; also elsewhere on the board
USB_ID: R129.1; also elsewhere on the board
V5: C33.2, C34.1, C38.2, C39.1, C95.2, C96.2, C97.2, R26.2, R33.1, R88.2, R92.2, R93.2, U68.13 (NC), U68.14 (VCC), U69.16 (VCC), U81.1 (VDD), U$25.1 (VCC); also elsewhere on the board
VUSB: F1.P$2, U71.8 (VCC)
XBE_RST: U$25.5 (~RESET); also elsewhere on the board
~485_RE: U68.3 (RE/); also elsewhere on the board

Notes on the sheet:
3V - 5.5V
Pin13 to VCC per Datasheet
USB Interface
